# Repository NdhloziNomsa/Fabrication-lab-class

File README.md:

# Fabrication-lab-class
This is a fablab class anything related to this class is here

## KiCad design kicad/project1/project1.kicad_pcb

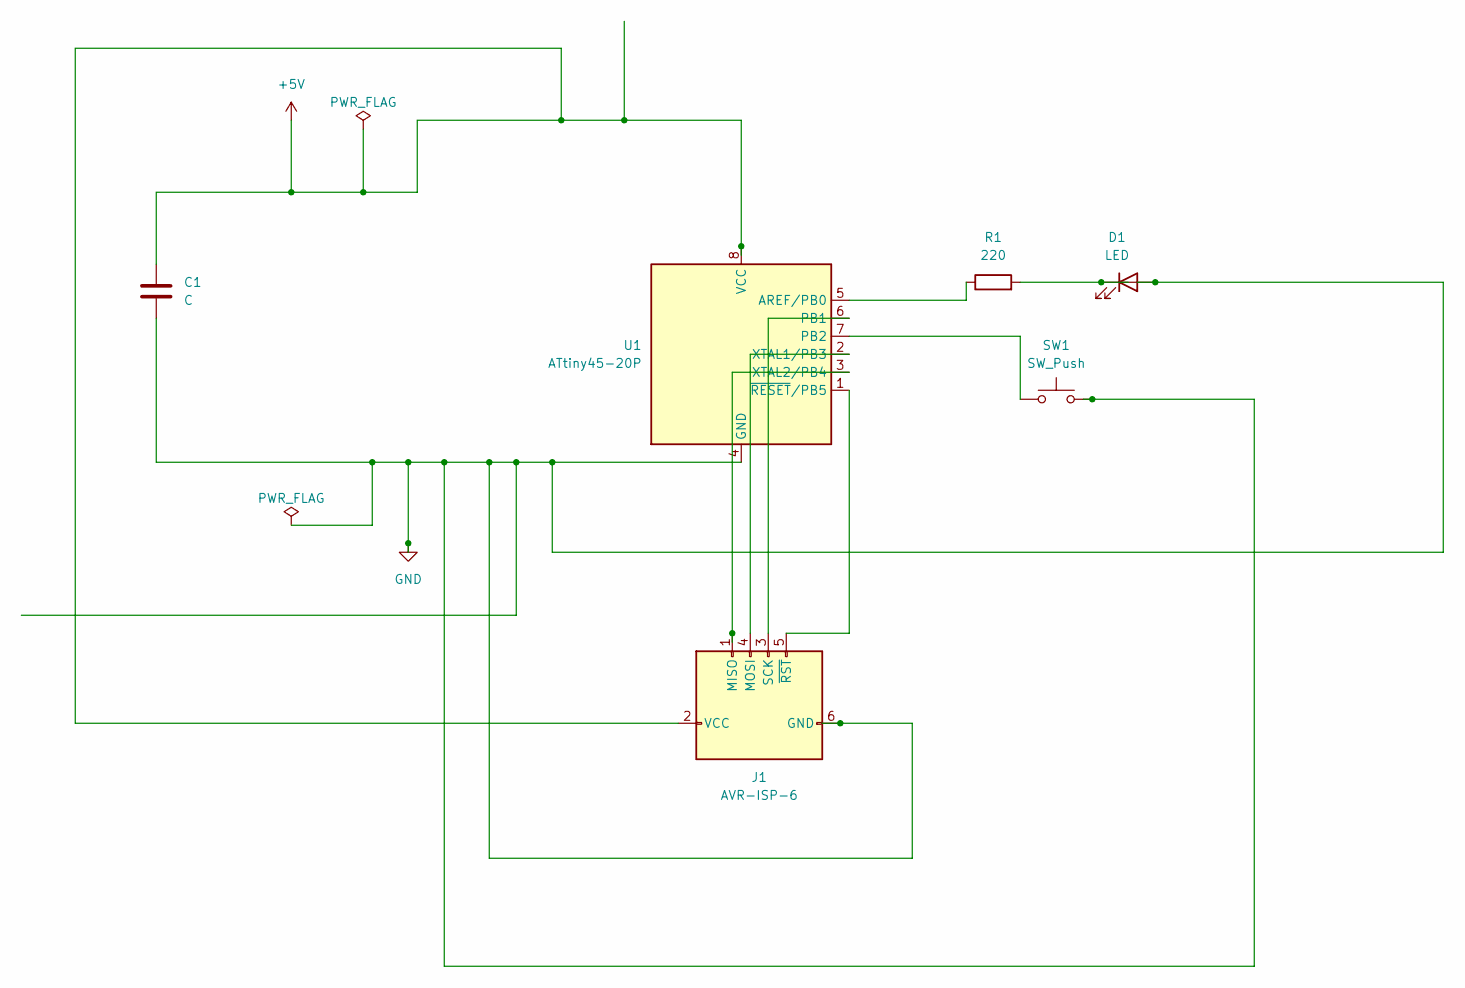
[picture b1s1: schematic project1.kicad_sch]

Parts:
C1: C; CP_Elec_3x5.3
D1: LED; LED_D4.0mm
J1: AVR-ISP-6; PinHeader_2x03_P2.00mm_Vertical
R1: 220; R_Axial_DIN0207_L6.3mm_D2.5mm_P7.62mm_Horizontal
SW1: SW_Push; SW_TH_Tactile_Omron_B3F-102x
U1: ATtiny45-20P; DIP-8_W7.62mm

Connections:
+5V: C1.1, J1.2 (VCC), U1.8 (VCC)
GND: C1.2, D1.2 (A), J1.6 (GND), SW1.2, U1.4 (GND)
unnamed: D1.1 (K), R1.2
unnamed: J1.1 (MISO), U1.3 (XTAL2/PB4)
unnamed: J1.4 (MOSI), U1.2 (XTAL1/PB3)
unnamed: J1.3 (SCK), U1.6 (PB1)
unnamed: J1.5 (~RST), U1.1 (~RESET/PB5)
unnamed: R1.1, U1.5 (AREF/PB0)
unnamed: SW1.1, U1.7 (PB2)

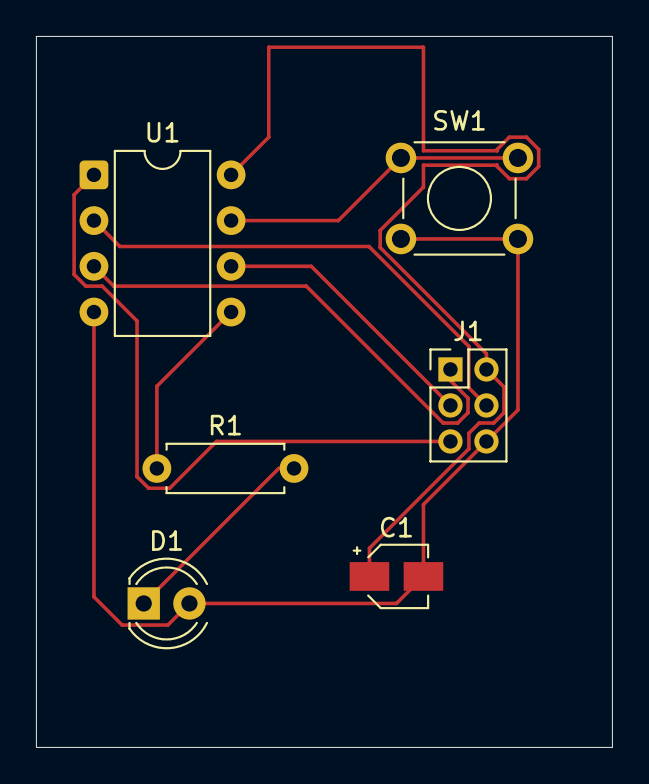
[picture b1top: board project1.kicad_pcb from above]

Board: 2 copper layers, 32.0 x 39.5 mm, 6 parts (0 on the bottom side), 9 nets.

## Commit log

2026-01-15 added files
2026-01-26 added freecad folder
2026-01-26 added inkscape folder
2026-01-26 added kicad folder
2026-01-30 uploaded remaining work after editing
2026-01-30 Deployed e77145c with MkDocs version: 1.6.1
2026-01-30 updated day 1 md file
2026-01-30 Deployed dc7685d with MkDocs version: 1.6.1
2026-01-30 edited more md files
2026-01-30 Deployed 5aaed47 with MkDocs version: 1.6.1
2026-01-30 Deployed dc57991 with MkDocs version: 1.6.1
